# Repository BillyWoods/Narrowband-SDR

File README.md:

# Narrowband-SDR
A four-channel narrowband SDR receiver based around the Mirics MSi001, Maxim MAX19777 and Cypress FX2LP.

|  |  |
|---|---|
|  |  |

## Project Layout
* Simulations of the RF architecture are in the **simulations/** folder.
* KiCAD PCB designs are in the **pcb/** folder.
* Firmware running on the Cypress FX2LP is stored in the **fx2fw/fx2sdr** folder. A copy of fx2lib is also included, which the firmware is built on, and fx2lib also provides utilities to upload/program the firmware to the device (fx2load).
* A branch of GNURadio (WiP) with support for this SDR is under development in the **host/** folder. However, at present data is pulled off the SDR and stored into raw files for later analysis using a tool in **fx2fw/uhd_driver**.

## Dependencies
fx2lib has a few dependencies, which are needed to compile the firmware:
* make
* gcc
* libusb-1.0
* SDCC
* python 2.7
* swig

Having libusb installed will also allow the host utility to be compiled.

## Acknowledgements
I would  like  to  thank Dr  Emanuele  Viterbo, of Monash University’s ECSE faculty, who supervised the project at its inception and assisted in developing its scope.

The open source Sigrok project must be acknowledged for serving as an example of how to use the FX2LP at the core of this SDR for high speed data acquisition.  Similarly, the Osmocom project, which provides a driver for the tuners used in this SDR, has assisted with interfacing and configuring the MSi001 tuners used in this project.

[Antti's LinuxTV Blog](http://blog.palosaari.fi/2013/10/naked-hardware-13-logitec-ldt-1s310uj.html) provided pictures of the PCB of an actual MSi001 implementation which were vital to developing the schematics for this project.

## Further Documentation
For more details on the project, see the [final report](deliverables/FYP_report_final.pdf).

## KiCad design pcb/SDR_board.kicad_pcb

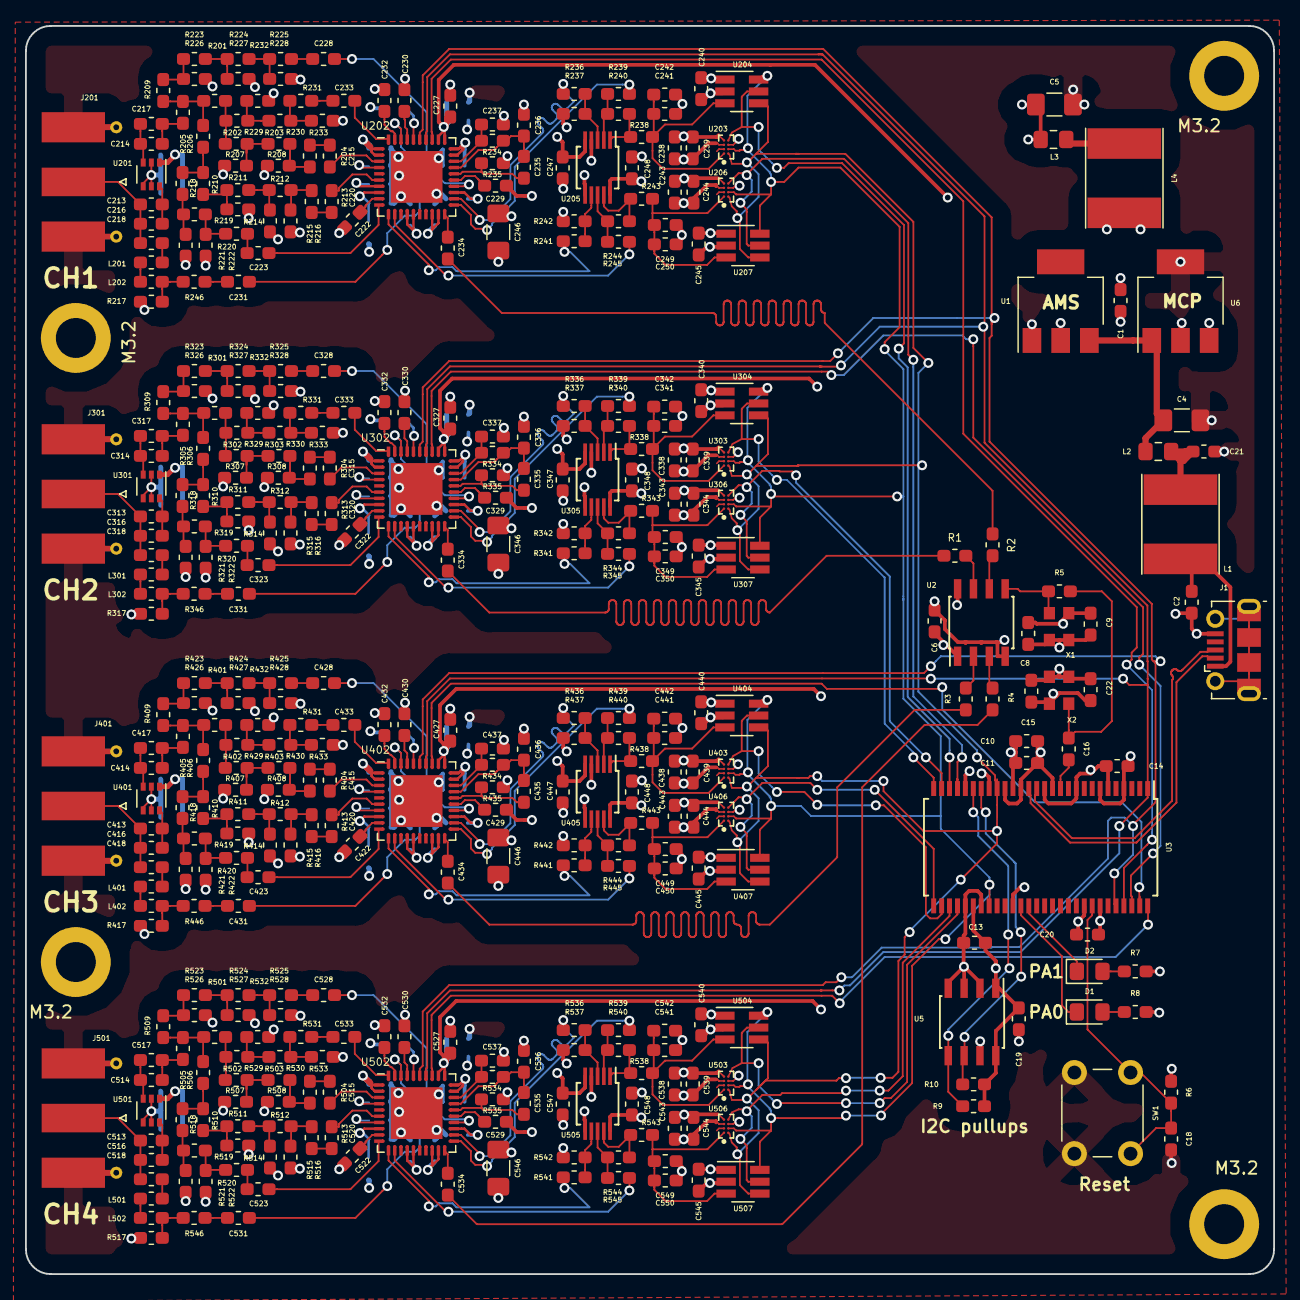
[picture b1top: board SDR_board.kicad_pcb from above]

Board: 4 copper layers, 100.0 x 100.0 mm, 467 parts (0 on the bottom side), 267 nets.

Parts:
C1, C2, C21, C226, C326, C426, C526: 1uF; C_0603_1608Metric_Pad1.05x0.95mm_HandSolder
C4, C5, C246, C346, C446, C546: 4.7uF; C_1206_3216Metric_Pad1.42x1.75mm_HandSolder
C6, C9, C15, C16, C230, C231, C234, C330, C331, C334, C430, C431, C434, C530, C531, C534: 1nF; C_0603_1608Metric_Pad1.05x0.95mm_HandSolder
C8, C10, C13, C14, C18, C20, C22, C201, C202, C218, C225, C239, C244, C248, C301, C302, C318, C325, C339, C344, C348, C401, C402, C418, C425, C439, C444, C448, C501, C502, C518, C525, C539, C544, C548: 0.1uF; C_0603_1608Metric_Pad1.05x0.95mm_HandSolder
C11, C19, C210, C212, C227, C238, C240, C243, C245, C247, C310, C312, C327, C338, C340, C343, C345, C347, C410, C412, C427, C438, C440, C443, C445, C447, C510, C512, C527, C538, C540, C543, C545, C547: 10nF; C_0603_1608Metric_Pad1.05x0.95mm_HandSolder
C203, C204, C205, C206, C207, C208, C209, C211, C213, C214, C216, C217, C228, C229, C241, C242, C249, C250, C303, C304, C305, C306, C307, C308, C309, C311, C313, C314, C316, C317, C328, C329, C341, C342, C349, C350, C403, C404, C405, C406, C407, C408, C409, C411, C413, C414, C416, C417, C428, C429, C441, C442, C449, C450, C503, C504, C505, C506, C507, C508, C509, C511, C513, C514, C516, C517, C528, C529, C541, C542, C549, C550: 100pF; C_0603_1608Metric_Pad1.05x0.95mm_HandSolder
C215, C219, C220, C221, C232, C233, C315, C319, C320, C321, C332, C333, C415, C419, C420, C421, C432, C433, C515, C519, C520, C521, C532, C533: 220pF; C_0603_1608Metric_Pad1.05x0.95mm_HandSolder
C222, C223, C322, C323, C422, C423, C522, C523: 390pF; C_0603_1608Metric_Pad1.05x0.95mm_HandSolder
C235, C335, C435, C535: 39nF; C_0603_1608Metric_Pad1.05x0.95mm_HandSolder
C236, C237, C336, C337, C436, C437, C536, C537: 2.7nF; C_0603_1608Metric_Pad1.05x0.95mm_HandSolder
D1, D2: LED; LED_0805_2012Metric_Pad1.15x1.40mm_HandSolder
J1: USB_B_Mini; USB_Micro-B_Molex-105017-0001
J201, J301, J401, J501: Molex 73251-1150 SMA; SMA_Molex_73251-1153_EdgeMount_Horizontal
L1, L4: 10uH; L_Taiyo-Yuden_NR-60xx_HandSoldering
L2, L3: 4.7uH; L_0805_2012Metric_Pad1.15x1.40mm_HandSolder
L201, L202, L301, L302, L401, L402, L501, L502: 150nH; L_0603_1608Metric_Pad1.05x0.95mm_HandSolder
M3.2, M3.2#2, M3.2#3, M3.2#4: MountingHole_3.2mm_M3_DIN965_Pad
R1, R2, R3, R4, R201, R205, R206, R301, R305, R306, R401, R405, R406, R501, R505, R506: 25; R_0603_1608Metric_Pad1.05x0.95mm_HandSolder
R5, R202, R203, R204, R207, R208, R210, R211, R212, R213, R214, R215, R216, R218, R219, R220, R221, R222, R223, R224, R225, R226, R227, R228, R229, R230, R231, R232, R233, R302, R303, R304, R307, R308, R310, R311, R312, R313, R314, R315, R316, R318, R319, R320, R321, R322, R323, R324, R325, R326, R327, R328, R329, R330, R331, R332, R333, R402, R403, R404, R407, R408, R410, R411, R412, R413, R414, R415, R416, R418, R419, R420, R421, R422, R423, R424, R425, R426, R427, R428, R429, R430, R431, R432, R433, R502, R503, R504, R507, R508, R510, R511, R512, R513, R514, R515, R516, R518, R519, R520, R521, R522, R523, R524, R525, R526, R527, R528, R529, R530, R531, R532, R533: 0; R_0603_1608Metric_Pad1.05x0.95mm_HandSolder
R6, R237, R242, R337, R342, R437, R442, R537, R542: 20k; R_0603_1608Metric_Pad1.05x0.95mm_HandSolder
R7, R8: 1k; R_0603_1608Metric_Pad1.05x0.95mm_HandSolder
R9, R10: 2.2k; R_0603_1608Metric_Pad1.05x0.95mm_HandSolder
R209, R217, R309, R317, R409, R417, R509, R517: 50; R_0603_1608Metric_Pad1.05x0.95mm_HandSolder
R234, R334, R434, R534: 499R; R_0603_1608Metric_Pad1.05x0.95mm_HandSolder
R235, R335, R435, R535: 360R; R_0603_1608Metric_Pad1.05x0.95mm_HandSolder
R236, R238, R241, R243, R246, R336, R338, R341, R343, R346, R436, R438, R441, R443, R446, R536, R538, R541, R543, R546: 0R; R_0603_1608Metric_Pad1.05x0.95mm_HandSolder
R239, R244, R339, R344, R439, R444, R539, R544: 40.2k; R_0603_1608Metric_Pad1.05x0.95mm_HandSolder
R240, R245, R340, R345, R440, R445, R540, R545: 10k; R_0603_1608Metric_Pad1.05x0.95mm_HandSolder
SW1: SW_Push; SW_PUSH_6mm_H5mm
U1: AMS1117-3.3; SOT-223
U2: NB3L553; SOIC-8_3.9x4.9mm_P1.27mm
U3: CY7C68013A-56PVX; SSOP-56_7.5x18.5mm_P0.635mm
U5: 24LC128; SOIC-8_3.9x4.9mm_P1.27mm
U6: MCP1825S; SOT-223-3_TabPin2
U201, U301, U401, U501: BGA2803; SOT-363_SC-70-6
U202, U302, U402, U502: MSi001-Q40; Texas_S-PVQFN-N40_EP4.15x4.15mm_less_solder_resist
U203, U206, U303, U306, U403, U406, U503, U506: MAX19777AZA+; BGA8N35P2X4_85X143X37N
U204, U207, U304, U307, U404, U407, U504, U507: ADS7883; SOT-23-6_Handsoldering
U205, U305, U405, U505: LMV712-N; MSOP-10_3x3mm_P0.5mm
X1, X2: XO32; Oscillator_SMD_EuroQuartz_XO32-4Pin_3.2x2.5mm

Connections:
+3.3VA: C5.1, C201.2, C202.2, C203.1, C204.1, C205.1, C206.1, C207.1, C208.1, C209.1, C210.1, C211.2, C212.1, C238.1, C239.2, C240.1, C243.1, C244.2, C245.1, C246.1, C247.1, C248.1, C301.2, C302.2, C303.1, C304.1, C305.1, C306.1, C307.1, C308.1, C309.1, C310.1, C311.2, C312.1, C338.1, C339.2, C340.1, C343.1, C344.2, C345.1, C346.1, C347.1, C348.1, C401.2, C402.2, C403.1, C404.1, C405.1, C406.1, C407.1, C408.1, C409.1, C410.1, C411.2, C412.1, C438.1, C439.2, C440.1, C443.1, C444.2, C445.1, C446.1, C447.1, C448.1, C501.2, C502.2, C503.1, C504.1, C505.1, C506.1, C507.1, C508.1, C509.1, C510.1, C511.2, C512.1, C538.1, C539.2, C540.1, C543.1, C544.2, C545.1, C546.1, C547.1, C548.1, L3.1, U201.1, U202.1, U202.2, U202.8, U202.14, U202.15, U202.18, U202.19, U202.23, U202.29, U202.30, U202.36, U203.A4, U204.1, U205.5, U205.6, U205.10, U206.A4, U207.1, U301.1, U302.1, U302.2, U302.8, U302.14, U302.15, U302.18, U302.19, U302.23, U302.29, U302.30, U302.36, U303.A4, U304.1, U305.5, U305.6, U305.10, U306.A4, U307.1, U401.1, U402.1, U402.2, U402.8, U402.14, U402.15, U402.18, U402.19, U402.23, U402.29, U402.30, U402.36, U403.A4, U404.1, U405.5, U405.6, U405.10, U406.A4, U407.1, U501.1, U502.1, U502.2, U502.8, U502.14, U502.15, U502.18, U502.19, U502.23, U502.29, U502.30, U502.36, U503.A4, U504.1, U505.5, U505.6, U505.10, U506.A4, U507.1
+3V3: C1.1, C6.1, C8.1, C9.1, C10.1, C11.1, C13.1, C14.1, C15.1, C19.1, C20.1, C22.1, C225.2, C226.2, C227.1, C325.2, C326.2, C327.1, C425.2, C426.2, C427.1, C525.2, C526.2, C527.1, L4.2, R6.1, R7.1, R8.1, R9.1, R10.1, U1.2, U2.1, U2.8, U3.6, U3.10, U3.14, U3.18, U3.24, U3.34, U3.39, U3.50, U5.1, U5.8, U6.3, U202.31, U202.32, U302.31, U302.32, U402.31, U402.32, U502.31, U502.32, X1.1, X1.4, X2.1, X2.4
/Channel 1/AM2_B3_MATCH: R201.1, R202.2, R229.2
/Channel 1/B45_VHF_MATCH: R206.1, R210.2, R218.2
/Channel 1/BUFFERED_SINGLE_I: C249.1, C250.1, R243.1, U206.A1, U207.3
/Channel 1/BUFFERED_SINGLE_Q: C241.1, C242.1, R238.1, U203.A1, U204.3
/Channel 1/I_DOUT: U3.25, U206.B4, U207.5
/Channel 1/I_N: R244.2, U202.12
/Channel 1/I_P: R241.2, U202.11
/Channel 1/L_MATCH: R209.1, R223.2, R226.2
/Channel 1/Q_DOUT: U3.26, U203.B4, U204.5
/Channel 1/Q_N: R239.2, U202.21
/Channel 1/Q_P: R236.2, U202.22
/Channel 1/high-Z: C231.2, R246.1
/Channel 2/AM2_B3_MATCH: R301.1, R302.2, R329.2
/Channel 2/B45_VHF_MATCH: R306.1, R310.2, R318.2
/Channel 2/BUFFERED_SINGLE_I: C349.1, C350.1, R343.1, U306.A1, U307.3
/Channel 2/BUFFERED_SINGLE_Q: C341.1, C342.1, R338.1, U303.A1, U304.3
/Channel 2/I_DOUT: U3.27, U306.B4, U307.5
/Channel 2/I_N: R344.2, U302.12
/Channel 2/I_P: R341.2, U302.11
/Channel 2/L_MATCH: R309.1, R323.2, R326.2
/Channel 2/Q_DOUT: U3.28, U303.B4, U304.5
/Channel 2/Q_N: R339.2, U302.21
/Channel 2/Q_P: R336.2, U302.22
/Channel 2/high-Z: C331.2, R346.1
/Channel 3/AM2_B3_MATCH: R401.1, R402.2, R429.2
/Channel 3/B45_VHF_MATCH: R406.1, R410.2, R418.2
/Channel 3/BUFFERED_SINGLE_I: C449.1, C450.1, R443.1, U406.A1, U407.3
/Channel 3/BUFFERED_SINGLE_Q: C441.1, C442.1, R438.1, U403.A1, U404.3
/Channel 3/I_DOUT: U3.29, U406.B4, U407.5
/Channel 3/I_N: R444.2, U402.12
/Channel 3/I_P: R441.2, U402.11
/Channel 3/L_MATCH: R409.1, R423.2, R426.2
/Channel 3/Q_DOUT: U3.30, U403.B4, U404.5
/Channel 3/Q_N: R439.2, U402.21
/Channel 3/Q_P: R436.2, U402.22
/Channel 3/high-Z: C431.2, R446.1
/Channel 4/AM2_B3_MATCH: R501.1, R502.2, R529.2
/Channel 4/B45_VHF_MATCH: R506.1, R510.2, R518.2
/Channel 4/BUFFERED_SINGLE_I: C549.1, C550.1, R543.1, U506.A1, U507.3
/Channel 4/BUFFERED_SINGLE_Q: C541.1, C542.1, R538.1, U503.A1, U504.3
/Channel 4/I_DOUT: U3.31, U506.B4, U507.5
/Channel 4/I_N: R544.2, U502.12
/Channel 4/I_P: R541.2, U502.11
/Channel 4/L_MATCH: R509.1, R523.2, R526.2
/Channel 4/Q_DOUT: U3.32, U503.B4, U504.5
/Channel 4/Q_N: R539.2, U502.21
/Channel 4/Q_P: R536.2, U502.22
/Channel 4/high-Z: C531.2, R546.1
/D_N: J1.2, U3.16
/D_P: J1.3, U3.15
/TUNER_1_CLK: C234.2, R2.2
/TUNER_1_nCS: U3.53, U202.33
/TUNER_2_CLK: C334.2, R1.2
/TUNER_2_nCS: U3.54, U302.33
/TUNER_3_CLK: C434.2, R3.1
/TUNER_3_nCS: U3.55, U402.33
/TUNER_4_CLK: C534.2, R4.1
/TUNER_4_nCS: U3.56, U502.33
ADC_CLK: U3.20, U203.B1, U204.4, U206.B1, U207.4, U303.B1, U304.4, U306.B1, U307.4, U403.B1, U404.4, U406.B1, U407.4, U503.B1, U504.4, U506.B1, U507.4
ADC_nCS: U3.36, U203.B2, U204.6, U206.B2, U207.6, U303.B2, U304.6, U306.B2, U307.6, U403.B2, U404.6, U406.B2, U407.6, U503.B2, U504.6, U506.B2, U507.6
FX2LP_AUX_OSC: C16.1, R5.1, X2.3
GND: C1.2, C2.2, C4.2, C5.2, C6.2, C8.2, C9.2, C10.2, C11.2, C13.2, C14.2, C15.2, C18.2, C19.2, C20.2, C21.2, C22.2, C201.1, C202.1, C203.2, C204.2, C205.2, C206.2, C207.2, C208.2, C209.2, C210.2, C211.1, C212.2, C219.2, C221.2, C222.2, C225.1, C226.1, C227.2, C229.2, C230.2, C232.2, C236.2, C237.2, C238.2, C239.1, C240.2, C241.2, C242.2, C243.2, C244.1, C245.2, C246.2, C247.2, C248.2, C249.2, C250.2, C301.1, C302.1, C303.2, C304.2, C305.2, C306.2, C307.2, C308.2, C309.2, C310.2, C311.1, C312.2, C319.2, C321.2, C322.2, C325.1, C326.1, C327.2, C329.2, C330.2, C332.2, C336.2, C337.2, C338.2, C339.1, C340.2, C341.2, C342.2, C343.2, C344.1, C345.2, C346.2, C347.2, C348.2, C349.2, C350.2, C401.1, C402.1, C403.2, C404.2, C405.2, C406.2, C407.2, C408.2, C409.2, C410.2, C411.1, C412.2, C419.2, C421.2, C422.2, C425.1, C426.1, C427.2, C429.2, C430.2, C432.2, C436.2, C437.2, C438.2, C439.1, C440.2, C441.2, C442.2, C443.2, C444.1, C445.2, C446.2, C447.2, C448.2, C449.2, C450.2, C501.1, C502.1, C503.2, C504.2, C505.2, C506.2, C507.2, C508.2, C509.2, C510.2, C511.1, C512.2, C519.2, C521.2, C522.2, C525.1, C526.1, C527.2, C529.2, C530.2, C532.2, C536.2, C537.2, C538.2, C539.1, C540.2, C541.2, C542.2, C543.2, C544.1, C545.2, C546.2, C547.2, C548.2, C549.2, C550.2, J1.5, J201.2, J301.2, J401.2, J501.2, R207.1, R208.1, R214.1, R215.1, R216.1, R217.2, R221.1, R222.1, R226.1, R227.1, R228.1, R232.1, R233.1, R235.1, R237.1, R242.1, R307.1, R308.1, R314.1, R315.1, R316.1, R317.2, R321.1, R322.1, R326.1, R327.1, R328.1, R332.1, R333.1, R335.1, R337.1, R342.1, R407.1, R408.1, R414.1, R415.1, R416.1, R417.2, R421.1, R422.1, R426.1, R427.1, R428.1, R432.1, R433.1, R435.1, R437.1, R442.1, R507.1, R508.1, R514.1, R515.1, R516.1, R517.2, R521.1, R522.1, R526.1, R527.1, R528.1, R532.1, R533.1, R535.1, R537.1, R542.1, SW1.2, U1.1, U2.4, U3.4, U3.7, U3.13, U3.17, U3.19, U3.21, U3.33, U3.35, U3.48, U5.2, U5.3, U5.4, U5.7, U6.2, U201.2, U201.4, U201.5, U202.41, U203.A3, U203.B3, U204.2, U205.4, U206.A3, U206.B3, U207.2, U301.2, U301.4, U301.5, U302.41, U303.A3, U303.B3, U304.2, U305.4, U306.A3, U306.B3, U307.2, U401.2, U401.4, U401.5, U402.41, U403.A3, U403.B3, U404.2, U405.4, U406.A3, U406.B3, U407.2, U501.2, U501.4, U501.5, U502.41, U503.A3, U503.B3, U504.2, U505.4, U506.A3, U506.B3, U507.2, X1.2, X2.2
unnamed: C4.1, L2.1, U1.3, U6.1
unnamed: C16.2, U3.12
unnamed: C18.1, R6.2, SW1.1, U3.49
unnamed: C21.1, L1.1, L2.2
unnamed: C213.1, C216.1, U201.6
unnamed: C213.2, C216.2, C218.2, J201.1
unnamed: C214.1, C217.1, R205.2
unnamed: C214.2, C217.2, U201.3
unnamed: C215.1, U202.3
unnamed: C215.2, R204.1
unnamed: C218.1, L201.1
unnamed: C219.1, U202.4
unnamed: C220.1, U202.6
unnamed: C220.2, R213.1
unnamed: C221.1, U202.7
unnamed: C222.1, U202.9
unnamed: C223.1, U202.10
unnamed: C223.2, R220.1
unnamed: C228.1, U202.24
unnamed: C228.2, R225.1
unnamed: C229.1, U202.25
unnamed: C230.1, U202.37
unnamed: C231.1, U202.38
unnamed: C232.1, U202.39
unnamed: C233.1, U202.40
unnamed: C233.2, R231.1
unnamed: C234.1, U202.20
unnamed: C235.1, C236.1, R234.1, U202.27
unnamed: C235.2, R235.2, U202.26
unnamed: C237.1, R234.2, U202.28
unnamed: C313.1, C316.1, U301.6
unnamed: C313.2, C316.2, C318.2, J301.1
unnamed: C314.1, C317.1, R305.2
unnamed: C314.2, C317.2, U301.3
unnamed: C315.1, U302.3
unnamed: C315.2, R304.1
unnamed: C318.1, L301.1
unnamed: C319.1, U302.4
unnamed: C320.1, U302.6
unnamed: C320.2, R313.1
unnamed: C321.1, U302.7
unnamed: C322.1, U302.9
unnamed: C323.1, U302.10
unnamed: C323.2, R320.1
unnamed: C328.1, U302.24
unnamed: C328.2, R325.1
unnamed: C329.1, U302.25
unnamed: C330.1, U302.37
unnamed: C331.1, U302.38
unnamed: C332.1, U302.39
unnamed: C333.1, U302.40
unnamed: C333.2, R331.1
unnamed: C334.1, U302.20
unnamed: C335.1, C336.1, R334.1, U302.27
unnamed: C335.2, R335.2, U302.26
unnamed: C337.1, R334.2, U302.28
unnamed: C413.1, C416.1, U401.6
unnamed: C413.2, C416.2, C418.2, J401.1
unnamed: C414.1, C417.1, R405.2
unnamed: C414.2, C417.2, U401.3
unnamed: C415.1, U402.3
unnamed: C415.2, R404.1
unnamed: C418.1, L401.1
unnamed: C419.1, U402.4
unnamed: C420.1, U402.6
unnamed: C420.2, R413.1
unnamed: C421.1, U402.7
unnamed: C422.1, U402.9
unnamed: C423.1, U402.10
unnamed: C423.2, R420.1
unnamed: C428.1, U402.24
unnamed: C428.2, R425.1
unnamed: C429.1, U402.25
unnamed: C430.1, U402.37
unnamed: C431.1, U402.38
unnamed: C432.1, U402.39
unnamed: C433.1, U402.40
unnamed: C433.2, R431.1
unnamed: C434.1, U402.20
unnamed: C435.1, C436.1, R434.1, U402.27
unnamed: C435.2, R435.2, U402.26
unnamed: C437.1, R434.2, U402.28
unnamed: C513.1, C516.1, U501.6
unnamed: C513.2, C516.2, C518.2, J501.1
unnamed: C514.1, C517.1, R505.2
unnamed: C514.2, C517.2, U501.3
unnamed: C515.1, U502.3
unnamed: C515.2, R504.1
unnamed: C518.1, L501.1
unnamed: C519.1, U502.4
unnamed: C520.1, U502.6
unnamed: C520.2, R513.1
unnamed: C521.1, U502.7
unnamed: C522.1, U502.9
unnamed: C523.1, U502.10
unnamed: C523.2, R520.1
unnamed: C528.1, U502.24
unnamed: C528.2, R525.1
unnamed: C529.1, U502.25
unnamed: C530.1, U502.37
unnamed: C531.1, U502.38
unnamed: C532.1, U502.39
unnamed: C533.1, U502.40
unnamed: C533.2, R531.1
unnamed: C534.1, U502.20
unnamed: C535.1, C536.1, R534.1, U502.27
unnamed: C535.2, R535.2, U502.26
unnamed: C537.1, R534.2, U502.28
unnamed: D1.1, U3.40
unnamed: D1.2, R8.2
unnamed: D2.1, U3.41
unnamed: D2.2, R7.2
unnamed: L3.2, L4.1
unnamed: L201.2, L202.1
unnamed: L202.2, R217.1, R246.2
unnamed: L301.2, L302.1
unnamed: L302.2, R317.1, R346.2
unnamed: L401.2, L402.1
unnamed: L402.2, R417.1, R446.2
unnamed: L501.2, L502.1
unnamed: L502.2, R517.1, R546.2
unnamed: R1.1, U2.7
unnamed: R2.1, U2.6
unnamed: R3.2, U2.2
unnamed: R4.2, U2.3
unnamed: R5.2, U2.5, X1.3
unnamed: R9.2, U3.23, U5.5
unnamed: R10.2, U3.22, U5.6
unnamed: R201.2, R205.1, R206.2, R209.2
unnamed: R202.1, R203.2, R207.2
unnamed: R203.1, R204.2, R208.2
unnamed: R210.1, R211.2, R214.2
unnamed: R211.1, R212.2, R215.2
unnamed: R212.1, R213.2, R216.2
unnamed: R218.1, R219.2, R221.2
unnamed: R219.1, R220.2, R222.2
unnamed: R223.1, R224.2, R227.2
unnamed: R224.1, R225.2, R228.2
unnamed: R229.1, R230.2, R232.2
unnamed: R230.1, R231.2, R233.2
unnamed: R236.1, R237.2, U205.3
unnamed: R238.2, R240.1, U205.1
unnamed: R239.1, R240.2, U205.2
unnamed: R241.1, R242.2, U205.7
unnamed: R243.2, R245.1, U205.9
unnamed: R244.1, R245.2, U205.8
unnamed: R301.2, R305.1, R306.2, R309.2
unnamed: R302.1, R303.2, R307.2
unnamed: R303.1, R304.2, R308.2
unnamed: R310.1, R311.2, R314.2
unnamed: R311.1, R312.2, R315.2
unnamed: R312.1, R313.2, R316.2
unnamed: R318.1, R319.2, R321.2
unnamed: R319.1, R320.2, R322.2
unnamed: R323.1, R324.2, R327.2
unnamed: R324.1, R325.2, R328.2
unnamed: R329.1, R330.2, R332.2
unnamed: R330.1, R331.2, R333.2
unnamed: R336.1, R337.2, U305.3
unnamed: R338.2, R340.1, U305.1
unnamed: R339.1, R340.2, U305.2
unnamed: R341.1, R342.2, U305.7
unnamed: R343.2, R345.1, U305.9
unnamed: R344.1, R345.2, U305.8
unnamed: R401.2, R405.1, R406.2, R409.2
unnamed: R402.1, R403.2, R407.2
unnamed: R403.1, R404.2, R408.2
unnamed: R410.1, R411.2, R414.2
unnamed: R411.1, R412.2, R415.2
unnamed: R412.1, R413.2, R416.2
unnamed: R418.1, R419.2, R421.2
unnamed: R419.1, R420.2, R422.2
unnamed: R423.1, R424.2, R427.2
unnamed: R424.1, R425.2, R428.2
unnamed: R429.1, R430.2, R432.2
unnamed: R430.1, R431.2, R433.2
unnamed: R436.1, R437.2, U405.3
unnamed: R438.2, R440.1, U405.1
unnamed: R439.1, R440.2, U405.2
unnamed: R441.1, R442.2, U405.7
unnamed: R443.2, R445.1, U405.9
unnamed: R444.1, R445.2, U405.8
unnamed: R501.2, R505.1, R506.2, R509.2
unnamed: R502.1, R503.2, R507.2
unnamed: R503.1, R504.2, R508.2
unnamed: R510.1, R511.2, R514.2
unnamed: R511.1, R512.2, R515.2
unnamed: R512.1, R513.2, R516.2
unnamed: R518.1, R519.2, R521.2
unnamed: R519.1, R520.2, R522.2
unnamed: R523.1, R524.2, R527.2
unnamed: R524.1, R525.2, R528.2
unnamed: R529.1, R530.2, R532.2
unnamed: R530.1, R531.2, R533.2
unnamed: R536.1, R537.2, U505.3
unnamed: R538.2, R540.1, U505.1
unnamed: R539.1, R540.2, U505.2
unnamed: R541.1, R542.2, U505.7
unnamed: R543.2, R545.1, U505.9
unnamed: R544.1, R545.2, U505.8
TUNER_SPI_CLK: U3.1, U202.34, U302.34, U402.34, U502.34
TUNER_SPI_MOSI: U3.52, U202.35, U302.35, U402.35, U502.35
VBUS: C2.1, J1.1, L1.2

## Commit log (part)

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2020-07-16 Added gitignore
2020-07-16 Added in all the files so far and updated README
2020-07-16 folder rename
2020-07-17 Drew circuit traces onto picture of existing msi001 implementation to assist with reverse engineering
2020-07-19 Started on an FPGA project which gets the FPGA to act like the ADC I plan to use (MAX11131), so data transfer back to the PC via the FX2LP can be developed
2020-07-19 Added testbenches, did some debugging through them
2020-07-20 antenna_input_coupling.asc: drew in all the circuitry that has been reverse-engineered so far
2020-07-20 Added deliverables into repo
2020-07-20 Changed over FPGA experiment to using the MAX19777 ADC, as this is what the project will be using now (8 of them)
2020-07-20 Proper sync'ing of SPI_slave
2020-07-20 Slowed down dbg clock and made CS go high a cycle later.
2020-07-20 Some screenshots and logic analyser capture results from the FPGA SPI ADC emulation
2020-07-21 Starting on a piece of FX2LP firmware to read from the ADCs/FPGA ADC emulator
2020-07-21 Bit of a shuffle round of files in fx2fw
2020-07-22 Starting with basic template for FX2LP GPIF design
2020-07-26 Added PC-side throughput test for transposing the form of data that we'll get over USB back into samples.
2020-07-26 More work on the sample transposition test; found a way to make it run fast with some bit math.
2020-07-27 Bitrate calculation was wrong. Corrected this to take into account we have 8 ADCs (channels)
2020-07-27 Changed to using a faster scheme for byte shuffling at the end of transpose to get our channels in order.
2020-07-27 amendment to previous commit
2020-08-06 In FPGA_SPI_slave, made each 'ADC' module increment by different amounts
2020-08-08 Added a little info to README
2020-08-08 Added a GPIF waveform which should be what we want for reading from these ADCs. Haven't tested yet though.
2020-08-08 Start of FX2LP firmware dedicated to this SDR project
2020-08-08 Some changes to gpif_config.gpf
2020-08-08 trying to base fw off fx2lafw
2020-08-09 Integrated the dscr.a51 from the sigrok project
2020-08-09 Fixed issue with reading device descriptor: this function needed to return something so the default would kick in
2020-08-09 Removed fx2lib's html docs from git
2020-08-09 Pulled endpoint initialisation code across from fx2lafw
2020-08-09 Moved all init into main_init
2020-08-09 on the trail of a bug; disabling this LED and timer stuff makes enumeration work again
2020-08-10 Corrected LED polarity for my board. Switched to using PORTA0. Bug: soon as timer 2 starts, USB enumeration fails.
2020-08-10 Changed fw memory layout to match fx2lafw
2020-08-10 added sdcc manual
2020-08-10 Got the timer2 interrupt working properly. The vector table wasn't getting written properly because there wasn't a predef of the TF2_ISR in the same file as main.
2020-08-10 Changed PID and VID to match the values before flashing (makes it easy to flash again when firmware is already loaded; don't have to reset)
2020-08-15 Started on the PC driver side of things
2020-08-15 Added IBN_ISR (in bulk NAK) handler to fx2fw, so we can tell when the host is requesting data
    Currently the system LED switches to blinking at a slower frequency when it NAKs on EP2IN
2020-08-19 The GPIF waveform is visible on the scope when we make a bulk IN request
2020-08-20 Added usb_sniffer script for looking at raw packets to/from the device
    wireshark seems to process these packets into a stream, which I don't always want
2020-08-20 Retry bulk tranfer UBR if unsuccessful
2020-08-21 Turns out I needed to gpif_read at index 0 to read into EP2. WTF?!
2020-08-21 Auto commit 504 byte packets.
2020-08-21 Made gpif waveform infinitely execute. Also got its length correct so there's 16 cycles.
2020-08-23 Added another .gpf file which I'm doing some rough working in
2020-08-23 Allowing this test waveform to go to the idle state seems to have helped
2020-08-23 stuffed up memcpy length!
2020-08-23 Added transposition so that we can see what's coming in on the channels a lot more easily
2020-08-23 Inverted clock output (so it appears as if we sample on the falling edge), gives more setup time. Trying it out.
    Also, the gpifwf ISR doesn't seem to trigger
2020-08-23 Added in second LED on this dev board. More debugging via LEDs--yay
2020-08-24 Bit of a milestone: GPIF waveform is well sorted out now
    gpif_waveforms.c is basically gpif_waveforms_simple.c but it steals the flowstate setup from gpif_waveforms_flow.c; we basically just need to set state 1 as the flowstate, capturing on rising and fal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
2020-08-26 Added reset to FPGA_SPI_slave and changed pin assignments to use 'fast' input and outputs
2020-08-28 Spice model for differential baseband outputs of tuner into ADC
2020-08-28 Building out the schematics; added the MAX19777
2020-08-28 Added a relevant datasheet, and the datasheet for another equivalent, but better, ADC
2020-08-29 More work on the PCB schematic
2020-09-01 Reverse engineering the VCO and loop filter stuff for the MSi001
2020-09-04 Some stuff on modelling the LNA DC blocking caps and how that part is connected up
2020-09-04 Resistive LNA to MSi001 coupling (is this useful/workable?)
2020-09-06 Added charge pump circuit to PCB schematic
2020-09-06 Reduced loop filter BW and avoided needing a new size of cap
2020-09-06 Just some changes that were hagning around.
2020-09-06 Split the inductors for the LP filter on input out into two smaller values, seems to correct for issues due to parasistic capacitance.
2020-09-06 Having a look at the power supply decoupling on the reverse engineered dongle
2020-09-06 Another, more hopeful attempt at a lazy resistive coupling between LNA and MSi001. This one has about 14dB of power loss to any given input. Pretty bad, but the LNA has 30dB gain.
2020-09-06 DC blocking cap for LF part of antenna coupling. Don't think we want to let DC currents flow through us.
2020-09-25 Added symbol for NB3L553 clock buffer/fanout
2020-09-25 Connected up the clock buffer
2020-09-25 Added in ADS7883 ADCs as the main ones
2020-09-27 more work on PCB
2020-09-27 Added second option for FX2LP clock source
2020-09-27 Duplicated the sheets for each channel.
2020-09-28 Annotated schematic, changed some pin types on the ADCs as DRC was unhappy
2020-09-28 Finished footprint selection.
2020-09-28 Changed power supply input filtering a bit
2020-09-28 Changed schematic symbol used for the SMA connector
2020-09-28 Schematic sheet size change
2020-09-28 Removed some clutter
2020-09-28 layout is in progress, got one channel and the digital stuff approximately laid out.
2020-09-29 more component layout
2020-09-29 Got a channel fully laid out. Setup trace profiles
2020-09-29 Tuner module mostly wired up, just gotta duplicate them and connect them together
2020-09-29 Added e14 parts list
2020-09-29 Stashing some possibly-breaking changes
2020-09-29 stashing some layout changes
2020-09-29 Resized component labels on silkscreen
2020-09-29 Added a version of the QFN40 package, used by the MSi001, with less solder resist.
2020-09-29 Closed solder resist around the MSi001 packages
2020-09-29 MSi001 was using rescued schematic symbol for some reason. Fixed this
2020-09-29 Added two missing series termination resistors on the clock buffer
2020-09-29 simplified SPI clock source for the MSi001
2020-09-29 Think the channels are done this time, for real
2020-09-30 Board layout complete
2020-09-30 Silkscreening done
2020-10-02 Removed unused GPIFWF ISR stuff (the flowstates take care of what I was trying to do here)
2020-10-03 LED1_TOGGLE macro had a small but crucial error
2020-10-03 Modified PC client to send vendor commands, and got LED2 to toggle on the board when it receives a vendor command
2020-10-03 Modified the client thingy to send whatever bRequest and data payload is passed to it
2020-10-04 Introduced code for SPI bit banging on the FX2LP (so far untested). Changed the vendor command to be geared towards sending the same thing to multiple channels in one transaction. Changed PC client t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
2020-10-04 Port D was getting locked up by some of the EPxFIFOCFG being left in whatever their initial state is (can't rely on it being zero apparently)
2020-10-04 Added the other modes to SPI, but the MSi001 datasheet indicates it uses mode 0, so won't bother testing the others too much
2020-10-13 In FPGA spi slave: added persistence for the same ADC read value over multiple read cycles
2020-10-13 extended amount of data being pulled off the FX2LP and got rid of a padding zero in the data print
2020-10-13 More logging of data
2020-10-14 Cloned in libmirisdr and libmirisdr-4 as submodules
2020-10-14 Revert "Removed libmirisdr as libmirisdr-4 supercedes it"
    This reverts commit 5e0119ecc36184173c0e2e9c8b9e17de59173ebf.
2020-10-21 Updated schematic to match some capacitors which were switched round in assembly
2020-10-21 Pulled the reserved pin of fx2lp to GND, per the fx2lp PCB dev guide
2020-10-24 Basically a script to find and replace silkscreen text attributes in bulk
2020-10-24 Some more datasheets and info on the FX2LP (including its IBIS file)
2020-10-24 Added generated gerbers for v0.1 into repo.
2020-10-24 Cleaned up submodules and added gr-osmosdr; got them to reference my forks (as we'll be modifying these repos).
2020-10-25 Added channel order flipping to the transpose code, as HW channels are flipped
2020-10-25 Also added channel order flipping to the raw ADC data retrieval tool
2020-10-25 Added commented out section to FW for choosing 30MHz clock (for debugging signal integrity).
2020-10-26 Added some SYNCDELAYs where they should be, but things were working prior anyway. Playing around with GPIF waveform termination conditions: upping the transaction count gives much smoother sampling
2020-10-26 implemented async libusb bulk reads.
2020-10-27 changed FPGA_SPI_slave dummy clock freqeuncy to 5MHz, as this is the slowest clock the GPIF can take in
2020-10-27 (Undo this commit soon) Small change to switch the GPIF onto an external clock
2020-10-27 Added flag for collection of raw (untransposed) values from the fx2lp
2020-10-27 Changed packet size to 507 bytes, as we'll collect data on 13 clock cycles now, rather than 12
    Trying to capture some zeros at the start of each ADC read for alignment
2020-10-27 Changed from storing 12 bits per ADC sample to 13 (the extra 0 bit allows for alignment)
    and looking at results, evidently consistent alignment between packets was not there
2020-10-27 Revert "Capturing on 16 clocks per ADC sample, was previously 13. (and a bunch of other changes to try and lazily avoid the need for packet alignment)"
    This reverts commit 4407046bb8bfd1232c1cb658693d012043e82c51.
2020-10-27 Had an off-by-one error in the GPIF waveform duration for state 1 (do the control signals get changed at the start or end of a state? I thought it was at the start)
2020-10-27 Make DP one state earlier in GPIF waveform
2020-10-28 Make GPIF waveform go into IDLE state when FIFO full flag is asserted
2020-10-28 Put the transaction counter back up to being massive
    Thanks to pausing on the FIFO full flag, packets are coming through properly aligned--no more missing data.
2020-10-28 Made transaction count a multiple of 13 (the number of reads we do per ADC sample)
2020-10-30 Tidy up of opamp circuit LTSpice
2020-10-30 Not having to manually send the tuning/config commands now!
2020-11-20 Hacked up a way to produce the data from one channel in complex normalised float32s. GQRX is happy with the output.
2020-11-22 Port D masking wasn't quite right for just the 4 nCS bits, 1:4, (bit 0, which does nothing, was being toggled).
2020-11-22 libmirisdr -> libfx2mirisdr
2021-01-01 Added FW support for 1.875 Msps, with vendor commands 0xB1 and 0xB2 to select b/w 3M and 1.875M
    This helps avoid dropping samples on a busy USB hub
2021-01-01 In FW: get gpif_acquisition_prepare to use the user-selected IFCLOCK speed
